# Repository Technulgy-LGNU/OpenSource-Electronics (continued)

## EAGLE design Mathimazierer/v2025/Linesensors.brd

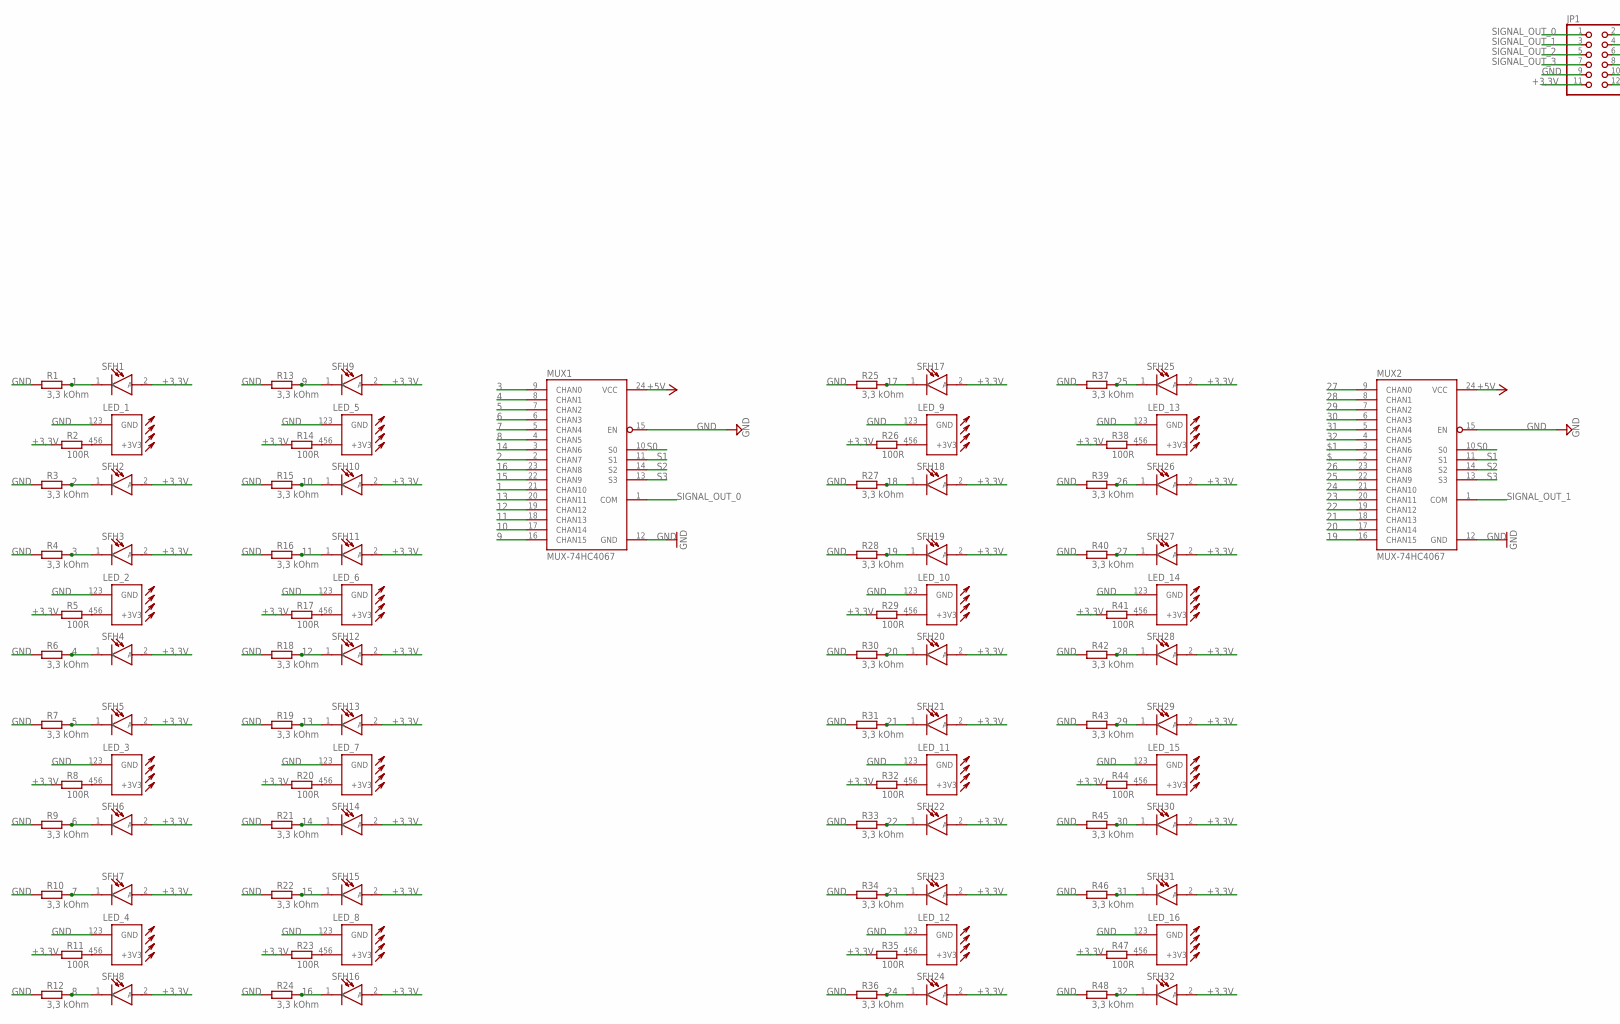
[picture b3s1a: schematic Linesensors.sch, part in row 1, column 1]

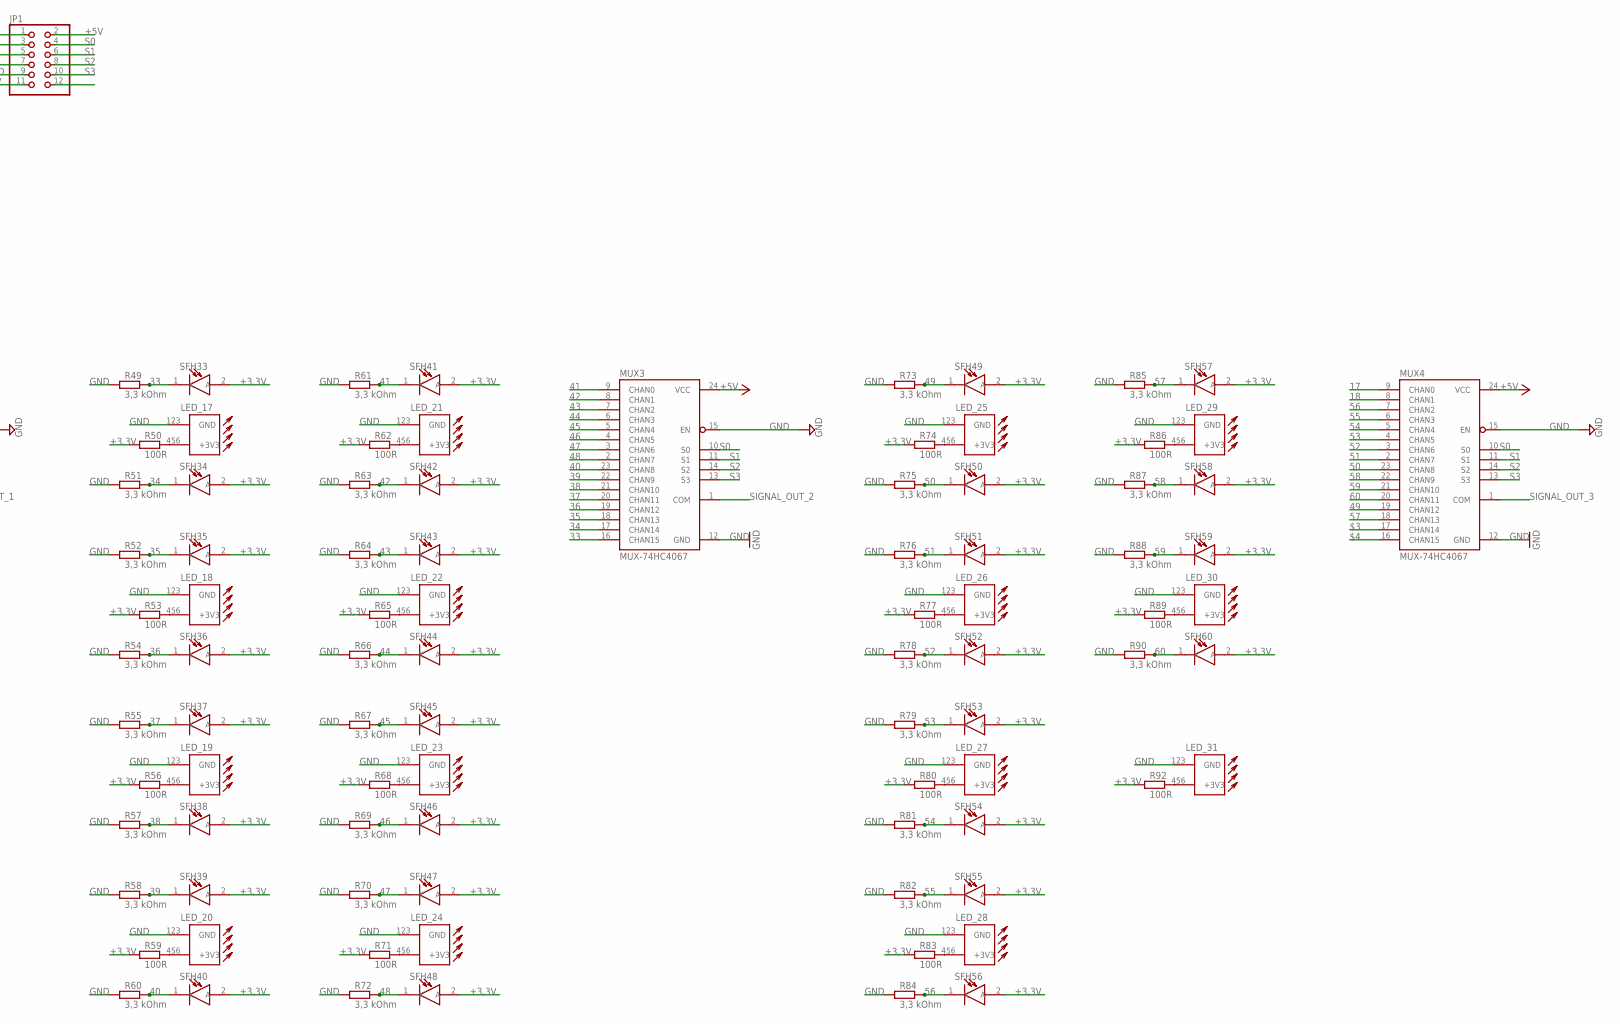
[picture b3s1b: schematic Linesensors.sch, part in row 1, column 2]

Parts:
JP1: PINHD-2X6; 2X06
LED_1, LED_2, LED_3, LED_4, LED_5, LED_6, LED_7, LED_8, LED_9, LED_10, LED_11, LED_12, LED_13, LED_14, LED_15, LED_16, LED_17, LED_18, LED_19, LED_20, LED_21, LED_22, LED_23, LED_24, LED_25, LED_26, LED_27, LED_28, LED_29, LED_30, LED_31: RND135-00056LEDD; LED
MUX1, MUX2, MUX3, MUX4: MUX-74HC4067; SSOP24
R1, R3, R4, R6, R7, R9, R10, R12, R13, R15, R16, R18, R19, R21, R22, R24, R25, R27, R28, R30, R31, R33, R34, R36, R37, R39, R40, R42, R43, R45, R46, R48, R49, R51, R52, R54, R55, R57, R58, R60, R61, R63, R64, R66, R67, R69, R70, R72, R73, R75, R76, R78, R79, R81, R82, R84, R85, R87, R88, R90: 3,3 kOhm; R1206
R2, R5, R8, R11, R14, R17, R20, R23, R26, R29, R32, R35, R38, R41, R44, R47, R50, R53, R56, R59, R62, R65, R68, R71, R74, R77, R80, R83, R86, R89, R92: 100R; R1206
SFH1, SFH2, SFH3, SFH4, SFH5, SFH6, SFH7, SFH8, SFH9, SFH10, SFH11, SFH12, SFH13, SFH14, SFH15, SFH16, SFH17, SFH18, SFH19, SFH20, SFH21, SFH22, SFH23, SFH24, SFH25, SFH26, SFH27, SFH28, SFH29, SFH30, SFH31, SFH32, SFH33, SFH34, SFH35, SFH36, SFH37, SFH38, SFH39, SFH40, SFH41, SFH42, SFH43, SFH44, SFH45, SFH46, SFH47, SFH48, SFH49, SFH50, SFH51, SFH52, SFH53, SFH54, SFH55, SFH56, SFH57, SFH58, SFH59, SFH60: SFH_3716; LEDC2012X89N

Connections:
1: MUX1.21 (CHAN10), R1.2, SFH1.1 (K)
2: MUX1.2 (CHAN7), R3.2, SFH2.1 (K)
3: MUX1.9 (CHAN0), R4.2, SFH3.1 (K)
4: MUX1.8 (CHAN1), R6.2, SFH4.1 (K)
5: MUX1.7 (CHAN2), R7.2, SFH5.1 (K)
6: MUX1.6 (CHAN3), R9.2, SFH6.1 (K)
7: MUX1.5 (CHAN4), R10.2, SFH7.1 (K)
8: MUX1.4 (CHAN5), R12.2, SFH8.1 (K)
9: MUX1.16 (CHAN15), R13.2, SFH9.1 (K)
10: MUX1.17 (CHAN14), R15.2, SFH10.1 (K)
11: MUX1.18 (CHAN13), R16.2, SFH11.1 (K)
12: MUX1.19 (CHAN12), R18.2, SFH12.1 (K)
13: MUX1.20 (CHAN11), R19.2, SFH13.1 (K)
14: MUX1.3 (CHAN6), R21.2, SFH14.1 (K)
15: MUX1.22 (CHAN9), R22.2, SFH15.1 (K)
16: MUX1.23 (CHAN8), R24.2, SFH16.1 (K)
17: MUX4.9 (CHAN0), R25.2, SFH17.1 (K)
18: MUX4.8 (CHAN1), R27.2, SFH18.1 (K)
19: MUX2.16 (CHAN15), R28.2, SFH19.1 (K)
20: MUX2.17 (CHAN14), R30.2, SFH20.1 (K)
21: MUX2.18 (CHAN13), R31.2, SFH21.1 (K)
22: MUX2.19 (CHAN12), R33.2, SFH22.1 (K)
23: MUX2.20 (CHAN11), R34.2, SFH23.1 (K)
24: MUX2.21 (CHAN10), R36.2, SFH24.1 (K)
25: MUX2.22 (CHAN9), R37.2, SFH25.1 (K)
26: MUX2.23 (CHAN8), R39.2, SFH26.1 (K)
27: MUX2.9 (CHAN0), R40.2, SFH27.1 (K)
28: MUX2.8 (CHAN1), R42.2, SFH28.1 (K)
29: MUX2.7 (CHAN2), R43.2, SFH29.1 (K)
30: MUX2.6 (CHAN3), R45.2, SFH30.1 (K)
31: MUX2.5 (CHAN4), R46.2, SFH31.1 (K)
32: MUX2.4 (CHAN5), R48.2, SFH32.1 (K)
33: MUX3.16 (CHAN15), R49.2, SFH33.1 (K)
34: MUX3.17 (CHAN14), R51.2, SFH34.1 (K)
35: MUX3.18 (CHAN13), R52.2, SFH35.1 (K)
36: MUX3.19 (CHAN12), R54.2, SFH36.1 (K)
37: MUX3.20 (CHAN11), R55.2, SFH37.1 (K)
38: MUX3.21 (CHAN10), R57.2, SFH38.1 (K)
39: MUX3.22 (CHAN9), R58.2, SFH39.1 (K)
40: MUX3.23 (CHAN8), R60.2, SFH40.1 (K)
41: MUX3.9 (CHAN0), R61.2, SFH41.1 (K)
42: MUX3.8 (CHAN1), R63.2, SFH42.1 (K)
43: MUX3.7 (CHAN2), R64.2, SFH43.1 (K)
44: MUX3.6 (CHAN3), R66.2, SFH44.1 (K)
45: MUX3.5 (CHAN4), R67.2, SFH45.1 (K)
46: MUX3.4 (CHAN5), R69.2, SFH46.1 (K)
47: MUX3.3 (CHAN6), R70.2, SFH47.1 (K)
48: MUX3.2 (CHAN7), R72.2, SFH48.1 (K)
49: MUX4.19 (CHAN12), R73.2, SFH49.1 (K)
50: MUX4.23 (CHAN8), R75.2, SFH50.1 (K)
51: MUX4.2 (CHAN7), R76.2, SFH51.1 (K)
52: MUX4.3 (CHAN6), R78.2, SFH52.1 (K)
53: MUX4.4 (CHAN5), R79.2, SFH53.1 (K)
54: MUX4.5 (CHAN4), R81.2, SFH54.1 (K)
55: MUX4.6 (CHAN3), R82.2, SFH55.1 (K)
56: MUX4.7 (CHAN2), R84.2, SFH56.1 (K)
57: MUX4.18 (CHAN13), R85.2, SFH57.1 (K)
58: MUX4.22 (CHAN9), R87.2, SFH58.1 (K)
59: MUX4.21 (CHAN10), R88.2, SFH59.1 (K)
60: MUX4.20 (CHAN11), R90.2, SFH60.1 (K)
$: MUX2.2 (CHAN7)
$1: MUX2.3 (CHAN6)
$3: MUX4.17 (CHAN14)
$4: MUX4.16 (CHAN15)
+3,3V: JP1.11, R2.1, R5.1, R8.1, R11.1, R14.1, R17.1, R20.1, R23.1, R26.1, R29.1, R32.1, R35.1, R38.1, R41.1, R44.1, R47.1, R50.1, R53.1, R56.1, R59.1, R62.1, R65.1, R68.1, R71.1, R74.1, R77.1, R80.1, R83.1, R86.1, R89.1, R92.1, SFH1.2 (A), SFH2.2 (A), SFH3.2 (A), SFH4.2 (A), SFH5.2 (A), SFH6.2 (A), SFH7.2 (A), SFH8.2 (A), SFH9.2 (A), SFH10.2 (A), SFH11.2 (A), SFH12.2 (A), SFH13.2 (A), SFH14.2 (A), SFH15.2 (A), SFH16.2 (A), SFH17.2 (A), SFH18.2 (A), SFH19.2 (A), SFH20.2 (A), SFH21.2 (A), SFH22.2 (A), SFH23.2 (A), SFH24.2 (A), SFH25.2 (A), SFH26.2 (A), SFH27.2 (A), SFH28.2 (A), SFH29.2 (A), SFH30.2 (A), SFH31.2 (A), SFH32.2 (A), SFH33.2 (A), SFH34.2 (A), SFH35.2 (A), SFH36.2 (A), SFH37.2 (A), SFH38.2 (A), SFH39.2 (A), SFH40.2 (A), SFH41.2 (A), SFH42.2 (A), SFH43.2 (A), SFH44.2 (A), SFH45.2 (A), SFH46.2 (A), SFH47.2 (A), SFH48.2 (A), SFH49.2 (A), SFH50.2 (A), SFH51.2 (A), SFH52.2 (A), SFH53.2 (A), SFH54.2 (A), SFH55.2 (A), SFH56.2 (A), SFH57.2 (A), SFH58.2 (A), SFH59.2 (A), SFH60.2 (A)
+5V: JP1.2, MUX1.24 (VCC), MUX2.24 (VCC), MUX3.24 (VCC), MUX4.24 (VCC)
ADFAF1: LED_2.456 (+3V3), R5.2
ADFAF2: LED_3.456 (+3V3), R8.2
ADFAF3: LED_4.456 (+3V3), R11.2
ADFAF4: LED_1.456 (+3V3), R2.2
ADFAF5: LED_5.456 (+3V3), R14.2
ADFAF6: LED_6.456 (+3V3), R17.2
ADFAF7: LED_7.456 (+3V3), R20.2
ADFAF8: LED_8.456 (+3V3), R23.2
ADFAF9: LED_9.456 (+3V3), R26.2
ADFAF10: LED_10.456 (+3V3), R29.2
ADFAF11: LED_11.456 (+3V3), R32.2
ADFAF12: LED_12.456 (+3V3), R35.2
ADFAF13: LED_13.456 (+3V3), R38.2
ADFAF14: LED_14.456 (+3V3), R41.2
ADFAF15: LED_15.456 (+3V3), R44.2
ADFAF16: LED_16.456 (+3V3), R47.2
ADFAF17: LED_17.456 (+3V3), R50.2
ADFAF18: LED_18.456 (+3V3), R53.2
ADFAF19: LED_19.456 (+3V3), R56.2
ADFAF20: LED_20.456 (+3V3), R59.2
ADFAF21: LED_21.456 (+3V3), R62.2
ADFAF22: LED_22.456 (+3V3), R65.2
ADFAF23: LED_23.456 (+3V3), R68.2
ADFAF24: LED_24.456 (+3V3), R71.2
ADFAF25: LED_25.456 (+3V3), R74.2
ADFAF26: LED_26.456 (+3V3), R77.2
ADFAF27: LED_27.456 (+3V3), R80.2
ADFAF28: LED_28.456 (+3V3), R83.2
ADFAF29: LED_29.456 (+3V3), R86.2
ADFAF30: LED_30.456 (+3V3), R89.2
ADFAF31: LED_31.456 (+3V3), R92.2
GND: JP1.9, LED_1.123 (GND), LED_2.123 (GND), LED_3.123 (GND), LED_4.123 (GND), LED_5.123 (GND), LED_6.123 (GND), LED_7.123 (GND), LED_8.123 (GND), LED_9.123 (GND), LED_10.123 (GND), LED_11.123 (GND), LED_12.123 (GND), LED_13.123 (GND), LED_14.123 (GND), LED_15.123 (GND), LED_16.123 (GND), LED_17.123 (GND), LED_18.123 (GND), LED_19.123 (GND), LED_20.123 (GND), LED_21.123 (GND), LED_22.123 (GND), LED_23.123 (GND), LED_24.123 (GND), LED_25.123 (GND), LED_26.123 (GND), LED_27.123 (GND), LED_28.123 (GND), LED_29.123 (GND), LED_30.123 (GND), LED_31.123 (GND), MUX1.12 (GND), MUX1.15 (EN), MUX2.12 (GND), MUX2.15 (EN), MUX3.12 (GND), MUX3.15 (EN), MUX4.12 (GND), MUX4.15 (EN), R1.1, R3.1, R4.1, R6.1, R7.1, R9.1, R10.1, R12.1, R13.1, R15.1, R16.1, R18.1, R19.1, R21.1, R22.1, R24.1, R25.1, R27.1, R28.1, R30.1, R31.1, R33.1, R34.1, R36.1, R37.1, R39.1, R40.1, R42.1, R43.1, R45.1, R46.1, R48.1, R49.1, R51.1, R52.1, R54.1, R55.1, R57.1, R58.1, R60.1, R61.1, R63.1, R64.1, R66.1, R67.1, R69.1, R70.1, R72.1, R73.1, R75.1, R76.1, R78.1, R79.1, R81.1, R82.1, R84.1, R85.1, R87.1, R88.1, R90.1
S0: JP1.4, MUX1.10 (S0), MUX2.10 (S0), MUX3.10 (S0), MUX4.10 (S0)
S1: JP1.6, MUX1.11 (S1), MUX2.11 (S1), MUX3.11 (S1), MUX4.11 (S1)
S2: JP1.8, MUX1.14 (S2), MUX2.14 (S2), MUX3.14 (S2), MUX4.14 (S2)
S3: JP1.10, MUX1.13 (S3), MUX2.13 (S3), MUX3.13 (S3), MUX4.13 (S3)
SIGNAL_OUT_0: JP1.1, MUX1.1 (COM)
SIGNAL_OUT_1: JP1.3, MUX2.1 (COM)
SIGNAL_OUT_2: JP1.5, MUX3.1 (COM)
SIGNAL_OUT_3: JP1.7, MUX4.1 (COM)

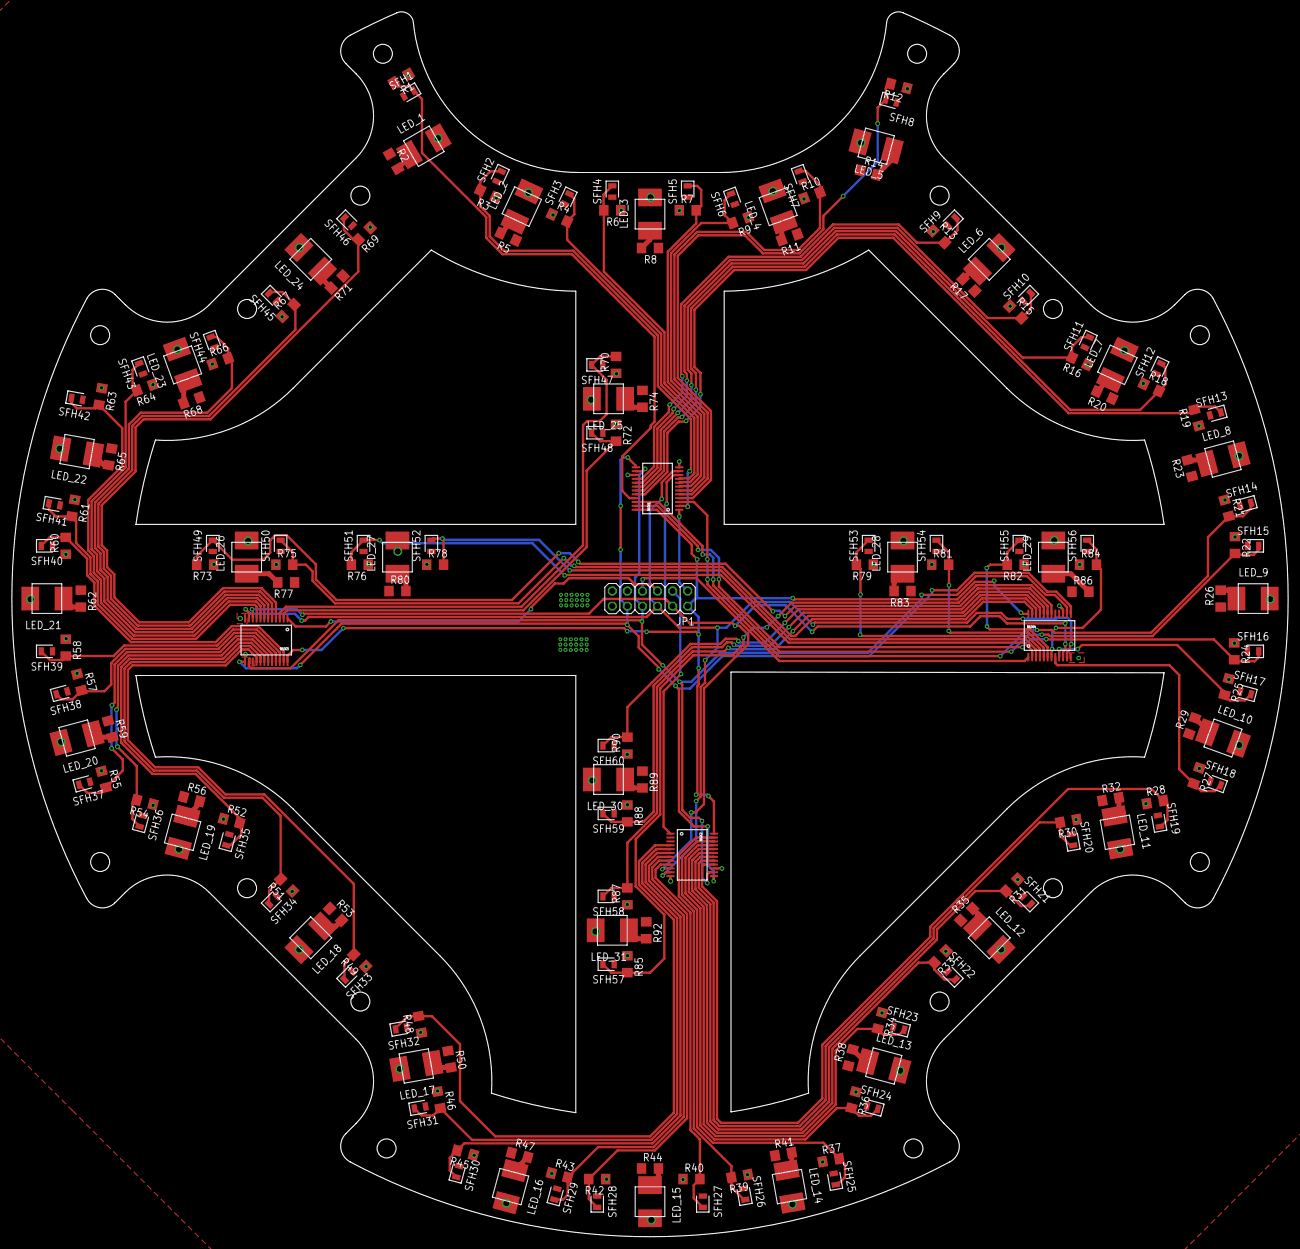
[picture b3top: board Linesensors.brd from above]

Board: 2 copper layers, 215.0 x 206.3 mm, 187 parts (0 on the bottom side), 102 nets.

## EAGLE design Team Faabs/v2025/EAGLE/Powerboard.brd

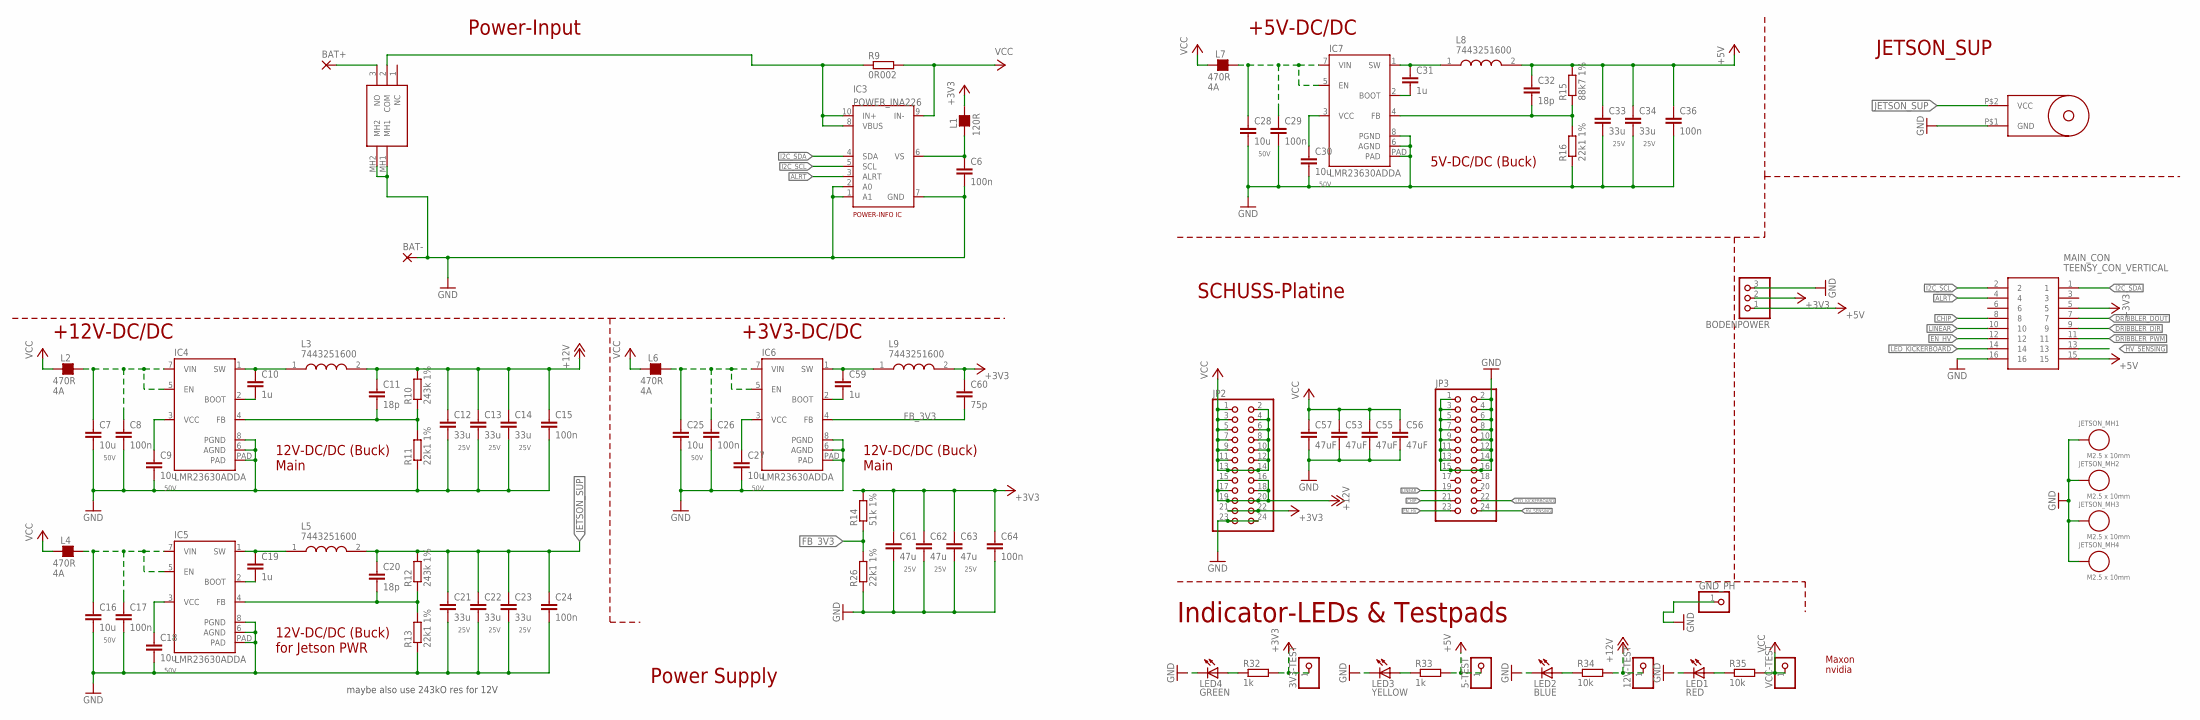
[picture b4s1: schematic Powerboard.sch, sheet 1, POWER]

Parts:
3V3-TEST, 5-TEST, 12V-TEST: PINHD-1X1; 1X01
BAT+: WIREPAD5,08/3; 5,08/3
BAT-: WIREPAD5,08/3; 5,08/3
BODENPOWER: PINHD-1X3; 1X03
C6, C8, C15, C17, C24, C26, C29, C36, C64: 100n; C0603
C7, C9, C16, C18, C25, C27, C28, C30: 10u; C1206; VOLTAGE 50V
C10, C19, C31, C59: 1u; C0603
C11, C20, C32: 18p; C0603
C12, C13, C14, C21, C22, C23, C33, C34: 33u; C1206; VOLTAGE 25V
C53, C55, C56, C57: 47uF; C1210
C60: 75p; C0603
C61, C62, C63: 47u; C1206; VOLTAGE 25V
GND_PH: PINHD-1X1; 1X01
IC3: POWER_INA226; TIGERS_DGS_S-PDSO-G10
IC4, IC5, IC6, IC7: LMR23630ADDA; TIGERS_DDA_R-PDSO-G8
JETSON_MH1, JETSON_MH2, JETSON_MH3, JETSON_MH4: M2.5 x 10mm; WA-SMSI_9774100151
JP2, JP3: PINHD-2X12; 2X12
L1: 120R; L0603
L2, L4, L6, L7: 470R; L1206
L3, L5, L8, L9: 7443251600; 7443251600_WE-HCI_105023
LED1: RED; POWER_DISTRIBUTION_CHIPLED_0805
LED2: BLUE; POWER_DISTRIBUTION_CHIPLED_0805
LED3: YELLOW; POWER_DISTRIBUTION_CHIPLED_0805
LED4: GREEN; POWER_DISTRIBUTION_CHIPLED_0805
MAIN_CON: TEENSY_CON_VERTICAL; 501645-1620_5016451620
R9: 0R002; R2512
R10, R12: 243k 1%; R0603
R11, R13, R16, R26: 22k1 1%; R0603
R14: 51k 1%; R0603
R15: 88k7 1%; R0603
R32, R33: 1k; R0603
R34, R35: 10k; R0603
S1: 500SSP1S1M6QEB
U$5: JETSON_ORIN-PWRJACK; PWRJACK
U$10: MAXON_LOGO
U$11: NVIDIA-LOGO
VCC-TEST: PINHD-1X1; 1X01

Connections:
+3V3: 3V3-TEST.1, BODENPOWER.2, C60.1, C61.1, C62.1, C63.1, C64.1, JP2.21, JP2.22, L1.2, L9.2, MAIN_CON.5, R14.2, R32.2
+5V: 5-TEST.1, BODENPOWER.1, C32.1, C33.1, C34.1, C36.1, L8.2, MAIN_CON.15, R15.2, R33.2
+12V: 12V-TEST.1, C11.1, C12.1, C13.1, C14.1, C15.1, JP2.15, JP2.16, JP2.17, JP2.18, JP2.19, JP2.20, L3.2, R10.2, R34.2; also elsewhere on the board
ALRT: IC3.3 (ALRT), MAIN_CON.4
BAT_SENSE2: IC3.8 (VBUS), IC3.10 (IN+), R9.1, S1.2 (COM)
BOOT_5V: C31.2, IC7.2 (BOOT)
BOOT_12V_1: C10.2, IC4.2 (BOOT)
BOOT_12V_2: C19.2, IC5.2 (BOOT)
BOOT_12V_4: C59.2, IC6.2 (BOOT)
CHIP: JP3.21, MAIN_CON.8
DRIBBLER_DIR: MAIN_CON.9; also elsewhere on the board
DRIBBLER_DOUT: MAIN_CON.7; also elsewhere on the board
DRIBBLER_PWM: MAIN_CON.11; also elsewhere on the board
EN_HV: JP3.23, MAIN_CON.12
FB_3V3: C60.2, IC6.4 (FB), R14.1, R26.2
FB_5V: C32.2, IC7.4 (FB), R15.1, R16.2
FB_12V_1: C11.2, IC4.4 (FB), R10.1, R11.2
FB_12V_2: C20.2, IC5.4 (FB), R12.1, R13.2
GND: BAT-.P$1, BODENPOWER.3, C6.2, C7.2, C8.2, C9.2, C12.2, C13.2, C14.2, C15.2, C16.2, C17.2, C18.2, C21.2, C22.2, C23.2, C24.2, C25.2, C26.2, C27.2, C28.2, C29.2, C30.2, C33.2, C34.2, C36.2, C53.2, C55.2, C56.2, C57.2, C61.2, C62.2, C63.2, C64.2, GND_PH.1, IC3.1 (A1), IC3.2 (A0), IC3.7 (GND), IC4.6 (AGND), IC4.8 (PGND), IC4.PAD, IC5.6 (AGND), IC5.8 (PGND), IC5.PAD, IC6.6 (AGND), IC6.8 (PGND), IC6.PAD, IC7.6 (AGND), IC7.8 (PGND), IC7.PAD, JETSON_MH1.1, JETSON_MH2.1, JETSON_MH3.1, JETSON_MH4.1, JP2.23, JP2.24, JP3.1, JP3.2, JP3.3, JP3.4, JP3.5, JP3.6, JP3.7, JP3.8, JP3.9, JP3.10, JP3.11, JP3.12, JP3.13, JP3.14, JP3.15, JP3.16, LED1.C, LED2.C, LED3.C, LED4.C, MAIN_CON.16, R11.1, R13.1, R16.1, R26.1, S1.MH1, S1.MH2, U$5.P$1 (GND); also elsewhere on the board
HV_SENSING: JP3.24, MAIN_CON.13
I2C_SCL: IC3.5 (SCL), MAIN_CON.2
I2C_SDA: IC3.4 (SDA), MAIN_CON.1
JETSON_SUP: C20.1, C21.1, C22.1, C23.1, C24.1, L5.2, R12.2, U$5.P$2 (VCC)
LED_KICKERBOARD: JP3.22, MAIN_CON.14
LINEAR: JP3.19, MAIN_CON.10
unnamed: BAT+.P$1, S1.3 (NO)
unnamed: LED1.A, R35.1
unnamed: LED4.A, R32.1
unnamed: LED3.A, R33.1
unnamed: LED2.A, R34.1
SW_3V3: C59.1, IC6.1 (SW), L9.1
SW_5V: C31.1, IC7.1 (SW), L8.1
SW_12V_1: C10.1, IC4.1 (SW), L3.1
SW_12V_2: C19.1, IC5.1 (SW), L5.1
VCC: C53.1, C55.1, C56.1, C57.1, IC3.9 (IN-), JP2.1, JP2.2, JP2.3, JP2.4, JP2.5, JP2.6, JP2.7, JP2.8, JP2.9, JP2.10, JP2.11, JP2.12, JP2.13, JP2.14, L2.1, L4.1, L6.1, L7.1, R9.2, R35.2, VCC-TEST.1; also elsewhere on the board
VCC_3V3: C27.1, IC6.3 (VCC)
VCC_5V: C30.1, IC7.3 (VCC)
VCC_12V_1: C9.1, IC4.3 (VCC)
VCC_12V_2: C18.1, IC5.3 (VCC)
VIN_3V3: C25.1, C26.1, IC6.5 (EN), IC6.7 (VIN), L6.2
VIN_5V: C28.1, C29.1, IC7.5 (EN), IC7.7 (VIN), L7.2
VIN_12V_1: C7.1, C8.1, IC4.5 (EN), IC4.7 (VIN), L2.2
VIN_12V_2: C16.1, C17.1, IC5.5 (EN), IC5.7 (VIN), L4.2
V_INA: C6.1, IC3.6 (VS), L1.1

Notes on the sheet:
Power Supply
SCHUSS-Platine
Power-Input
POWER-INFO IC
+12V-DC/DC
12V-DC/DC (Buck) for Jetson PWR
12V-DC/DC (Buck) Main
+3V3-DC/DC
5V-DC/DC (Buck)
+5V-DC/DC
JETSON_SUP
Indicator-LEDs & Testpads
maybe also use 243kO res for 12V

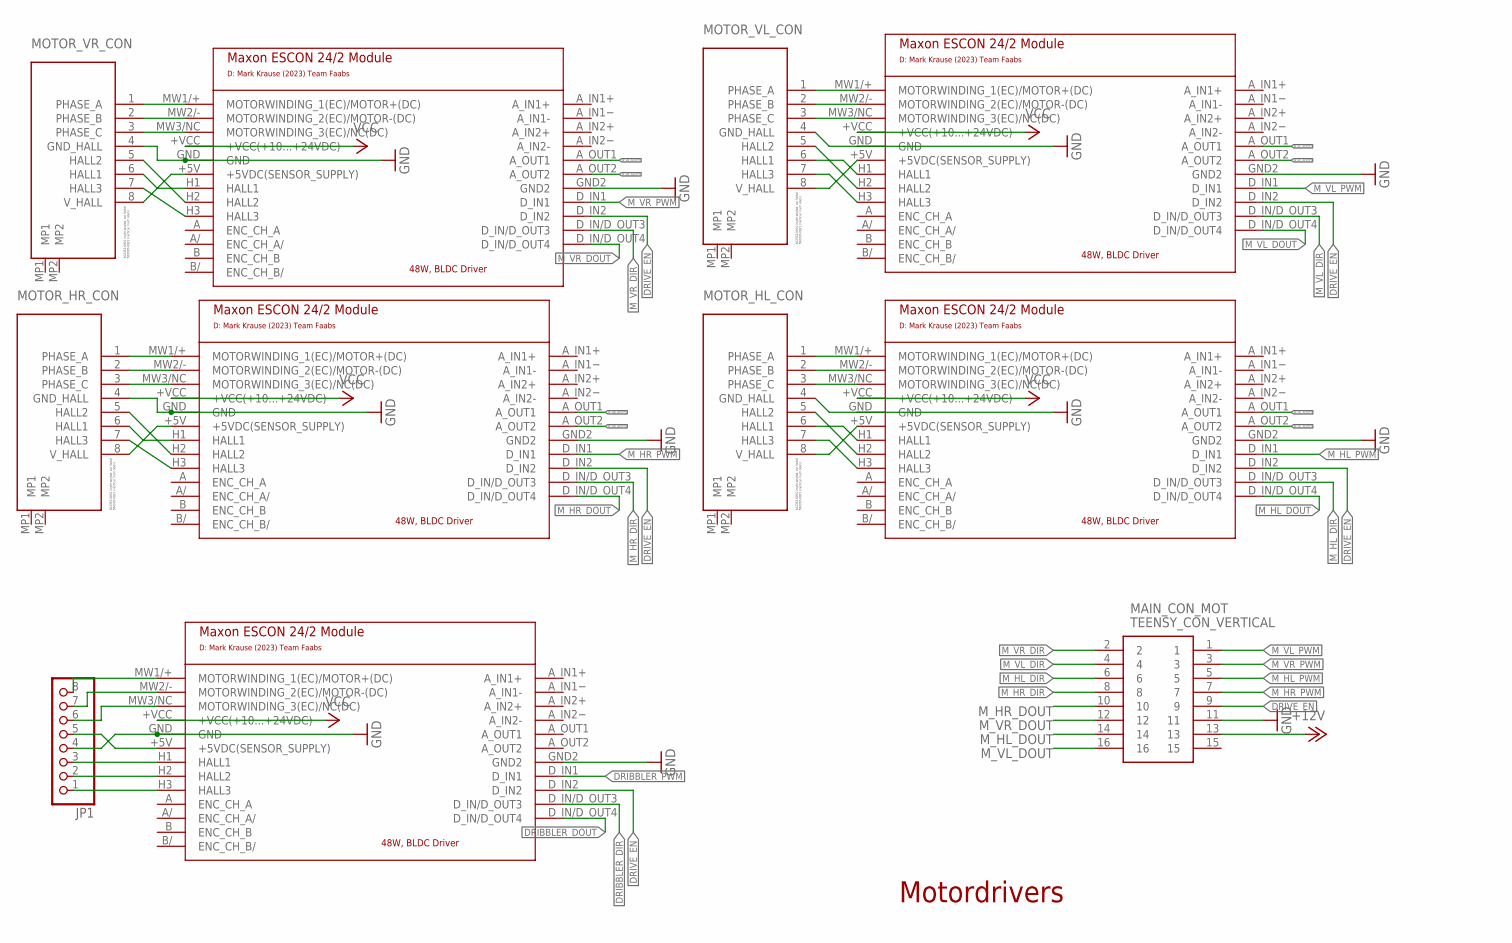
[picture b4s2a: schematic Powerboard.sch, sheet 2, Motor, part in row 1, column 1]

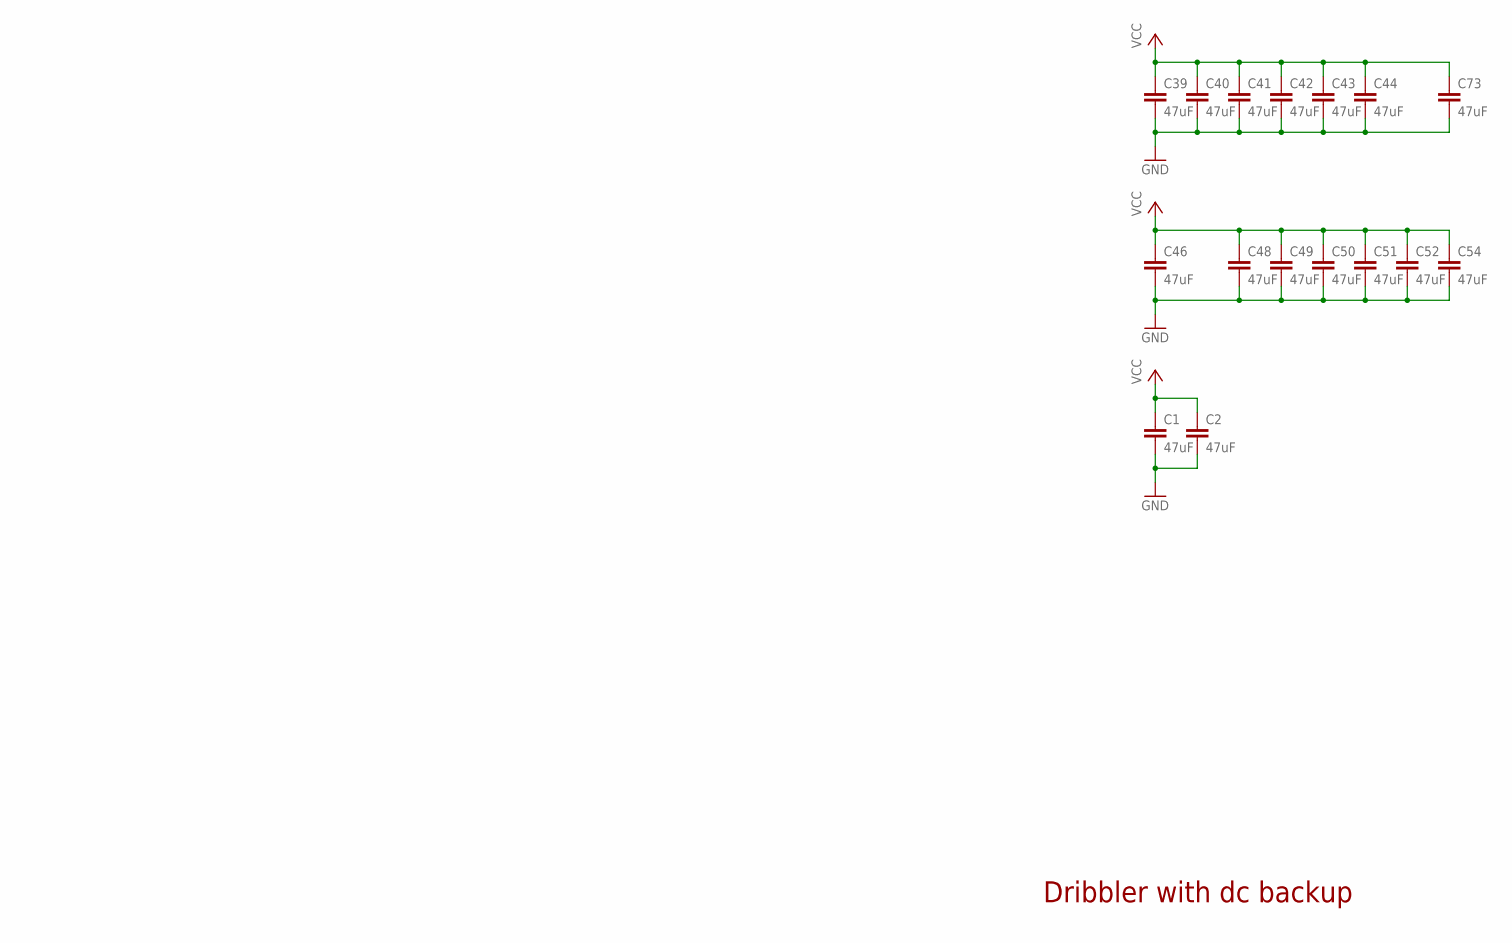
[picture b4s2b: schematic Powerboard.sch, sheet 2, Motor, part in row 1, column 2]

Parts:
C1, C2, C39, C40, C41, C42, C43, C44, C46, C48, C49, C50, C51, C52, C54, C73: 47uF; C1210
JP1: PINHD-1X8/90; 1X08/90
MAIN_CON_MOT: TEENSY_CON_VERTICAL; 501645-1620_5016451620
MOTOR_HL_CON: MOTOR_CONMOTOR_CON_VERTICAL; MOTOR_CON_VERTICAL
MOTOR_HR_CON: MOTOR_CONMOTOR_CON_VERTICAL; MOTOR_CON_VERTICAL
MOTOR_VL_CON: MOTOR_CONMOTOR_CON_VERTICAL; MOTOR_CON_VERTICAL
MOTOR_VR_CON: MOTOR_CONMOTOR_CON_VERTICAL; MOTOR_CON_VERTICAL
U$1, U$2, U$3, U$4, U$6: MAXON_ESCON24/2; MAXON_ESCON24/2_MODULE

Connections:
+12V: MAIN_CON_MOT.13; also elsewhere on the board
DRIBBLER_DIR: U$6.D_IN/D_OUT3; also elsewhere on the board
DRIBBLER_DOUT: U$6.D_IN/D_OUT4; also elsewhere on the board
DRIBBLER_PWM: U$6.D_IN1; also elsewhere on the board
DRIVE_EN: MAIN_CON_MOT.9, U$1.D_IN2, U$2.D_IN2, U$3.D_IN2, U$4.D_IN2, U$6.D_IN2
GND: C1.2, C2.2, C39.2, C40.2, C41.2, C42.2, C43.2, C44.2, C46.2, C48.2, C49.2, C50.2, C51.2, C52.2, C54.2, C73.2, MAIN_CON_MOT.11, MOTOR_HL_CON.4 (GND_HALL), MOTOR_HR_CON.4 (GND_HALL), MOTOR_VL_CON.4 (GND_HALL), MOTOR_VR_CON.4 (GND_HALL), U$1.GND, U$1.GND2, U$2.GND, U$2.GND2, U$3.GND, U$3.GND2, U$4.GND, U$4.GND2, U$6.GND2; also elsewhere on the board
MOTOR_D_A: JP1.8, U$6.MW1/+ (MOTORWINDING_1(EC)/MOTOR+(DC))
MOTOR_D_B: JP1.7, U$6.MW2/- (MOTORWINDING_2(EC)/MOTOR-(DC))
MOTOR_D_C: JP1.6, U$6.MW3/NC (MOTORWINDING_3(EC)/NC(DC))
MOTOR_D_H1: JP1.3, U$6.H1 (HALL1)
MOTOR_D_H2: JP1.2, U$6.H2 (HALL2)
MOTOR_D_H3: JP1.1, U$6.H3 (HALL3)
MOTOR_D_VHALL: JP1.5, U$6.+5V (+5VDC(SENSOR_SUPPLY))
MOTOR_HL_A: MOTOR_HL_CON.1 (PHASE_A), U$4.MW1/+ (MOTORWINDING_1(EC)/MOTOR+(DC))
MOTOR_HL_B: MOTOR_HL_CON.2 (PHASE_B), U$4.MW2/- (MOTORWINDING_2(EC)/MOTOR-(DC))
MOTOR_HL_C: MOTOR_HL_CON.3 (PHASE_C), U$4.MW3/NC (MOTORWINDING_3(EC)/NC(DC))
MOTOR_HL_H1: MOTOR_HL_CON.6 (HALL1), U$4.H1 (HALL1)
MOTOR_HL_H2: MOTOR_HL_CON.5 (HALL2), U$4.H2 (HALL2)
MOTOR_HL_H3: MOTOR_HL_CON.7 (HALL3), U$4.H3 (HALL3)
MOTOR_HL_VHALL: MOTOR_HL_CON.8 (V_HALL), U$4.+5V (+5VDC(SENSOR_SUPPLY))
MOTOR_HR_A: MOTOR_HR_CON.1 (PHASE_A), U$1.MW1/+ (MOTORWINDING_1(EC)/MOTOR+(DC))
MOTOR_HR_B: MOTOR_HR_CON.2 (PHASE_B), U$1.MW2/- (MOTORWINDING_2(EC)/MOTOR-(DC))
MOTOR_HR_C: MOTOR_HR_CON.3 (PHASE_C), U$1.MW3/NC (MOTORWINDING_3(EC)/NC(DC))
MOTOR_HR_H1: MOTOR_HR_CON.6 (HALL1), U$1.H1 (HALL1)
MOTOR_HR_H2: MOTOR_HR_CON.5 (HALL2), U$1.H2 (HALL2)
MOTOR_HR_H3: MOTOR_HR_CON.7 (HALL3), U$1.H3 (HALL3)
MOTOR_HR_VHALL: MOTOR_HR_CON.8 (V_HALL), U$1.+5V (+5VDC(SENSOR_SUPPLY))
MOTOR_VL_A: MOTOR_VL_CON.1 (PHASE_A), U$3.MW1/+ (MOTORWINDING_1(EC)/MOTOR+(DC))
MOTOR_VL_B: MOTOR_VL_CON.2 (PHASE_B), U$3.MW2/- (MOTORWINDING_2(EC)/MOTOR-(DC))
MOTOR_VL_C: MOTOR_VL_CON.3 (PHASE_C), U$3.MW3/NC (MOTORWINDING_3(EC)/NC(DC))
MOTOR_VL_H1: MOTOR_VL_CON.6 (HALL1), U$3.H1 (HALL1)
MOTOR_VL_H2: MOTOR_VL_CON.5 (HALL2), U$3.H2 (HALL2)
MOTOR_VL_H3: MOTOR_VL_CON.7 (HALL3), U$3.H3 (HALL3)
MOTOR_VL_VHALL: MOTOR_VL_CON.8 (V_HALL), U$3.+5V (+5VDC(SENSOR_SUPPLY))
MOTOR_VR_A: MOTOR_VR_CON.1 (PHASE_A), U$2.MW1/+ (MOTORWINDING_1(EC)/MOTOR+(DC))
MOTOR_VR_B: MOTOR_VR_CON.2 (PHASE_B), U$2.MW2/- (MOTORWINDING_2(EC)/MOTOR-(DC))
MOTOR_VR_C: MOTOR_VR_CON.3 (PHASE_C), U$2.MW3/NC (MOTORWINDING_3(EC)/NC(DC))
MOTOR_VR_H1: MOTOR_VR_CON.6 (HALL1), U$2.H1 (HALL1)
MOTOR_VR_H2: MOTOR_VR_CON.5 (HALL2), U$2.H2 (HALL2)
MOTOR_VR_H3: MOTOR_VR_CON.7 (HALL3), U$2.H3 (HALL3)
MOTOR_VR_VHALL: MOTOR_VR_CON.8 (V_HALL), U$2.+5V (+5VDC(SENSOR_SUPPLY))
M_HL_AOUT1: U$4.A_OUT1
M_HL_AOUT2: U$4.A_OUT2
M_HL_DIR: MAIN_CON_MOT.6, U$4.D_IN/D_OUT3
M_HL_DOUT: MAIN_CON_MOT.14, U$4.D_IN/D_OUT4
M_HL_PWM: MAIN_CON_MOT.5, U$4.D_IN1
M_HR_AOUT1: U$1.A_OUT1
M_HR_AOUT2: U$1.A_OUT2
M_HR_DIR: MAIN_CON_MOT.8, U$1.D_IN/D_OUT3
M_HR_DOUT: MAIN_CON_MOT.10, U$1.D_IN/D_OUT4
M_HR_PWM: MAIN_CON_MOT.7, U$1.D_IN1
M_VL_AOUT1: U$3.A_OUT1
M_VL_AOUT2: U$3.A_OUT2
M_VL_DIR: MAIN_CON_MOT.4, U$3.D_IN/D_OUT3
M_VL_DOUT: MAIN_CON_MOT.16, U$3.D_IN/D_OUT4
M_VL_PWM: MAIN_CON_MOT.1, U$3.D_IN1
M_VR_AOUT1: U$2.A_OUT1
M_VR_AOUT2: U$2.A_OUT2
M_VR_DIR: MAIN_CON_MOT.2, U$2.D_IN/D_OUT3
M_VR_DOUT: MAIN_CON_MOT.12, U$2.D_IN/D_OUT4
M_VR_PWM: MAIN_CON_MOT.3, U$2.D_IN1
unnamed: JP1.4, U$6.GND
VCC: C1.1, C2.1, C39.1, C40.1, C41.1, C42.1, C43.1, C44.1, C46.1, C48.1, C49.1, C50.1, C51.1, C52.1, C54.1, C73.1, U$1.+VCC (+VCC(+10...+24VDC)), U$2.+VCC (+VCC(+10...+24VDC)), U$3.+VCC (+VCC(+10...+24VDC)), U$4.+VCC (+VCC(+10...+24VDC)), U$6.+VCC (+VCC(+10...+24VDC)); also elsewhere on the board

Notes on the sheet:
Motordrivers
Dribbler with dc backup

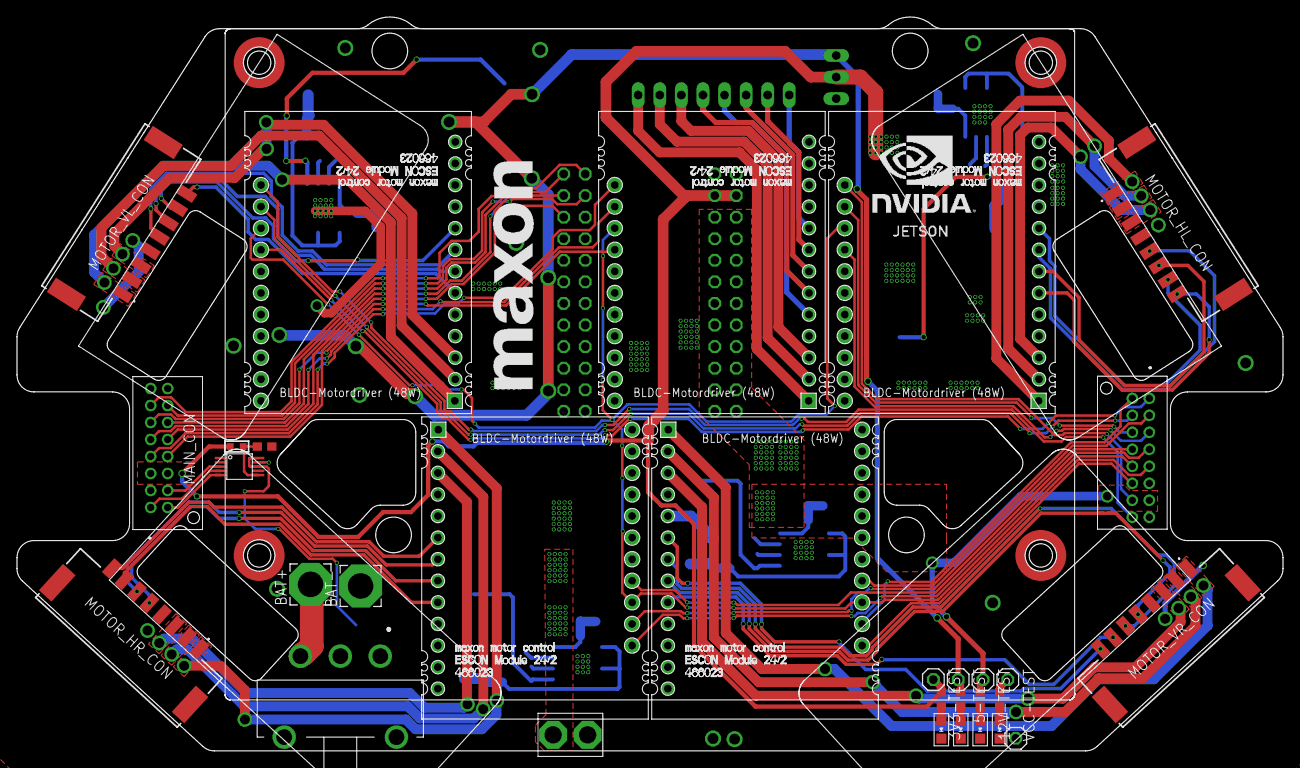
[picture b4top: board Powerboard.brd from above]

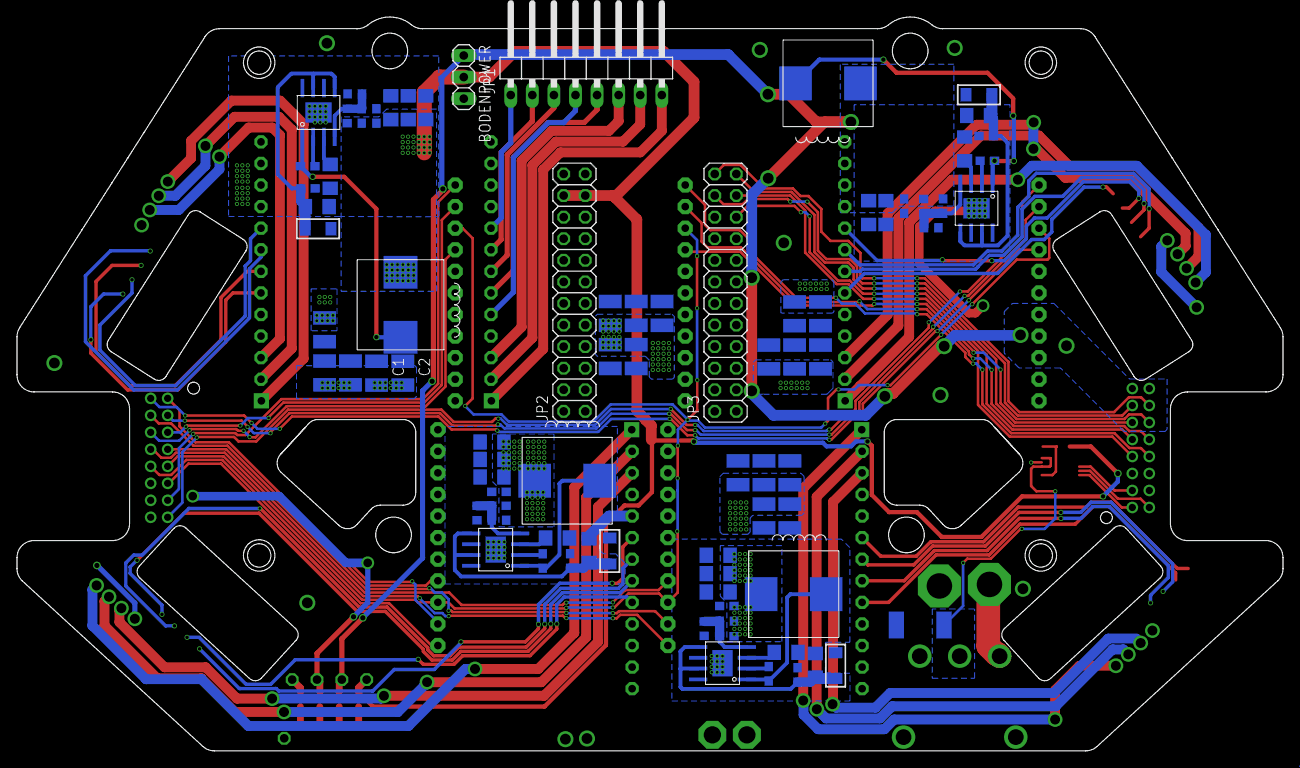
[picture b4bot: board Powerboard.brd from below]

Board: 2 copper layers, 149.0 x 86.4 mm, 117 parts (80 on the bottom side), 93 nets.
